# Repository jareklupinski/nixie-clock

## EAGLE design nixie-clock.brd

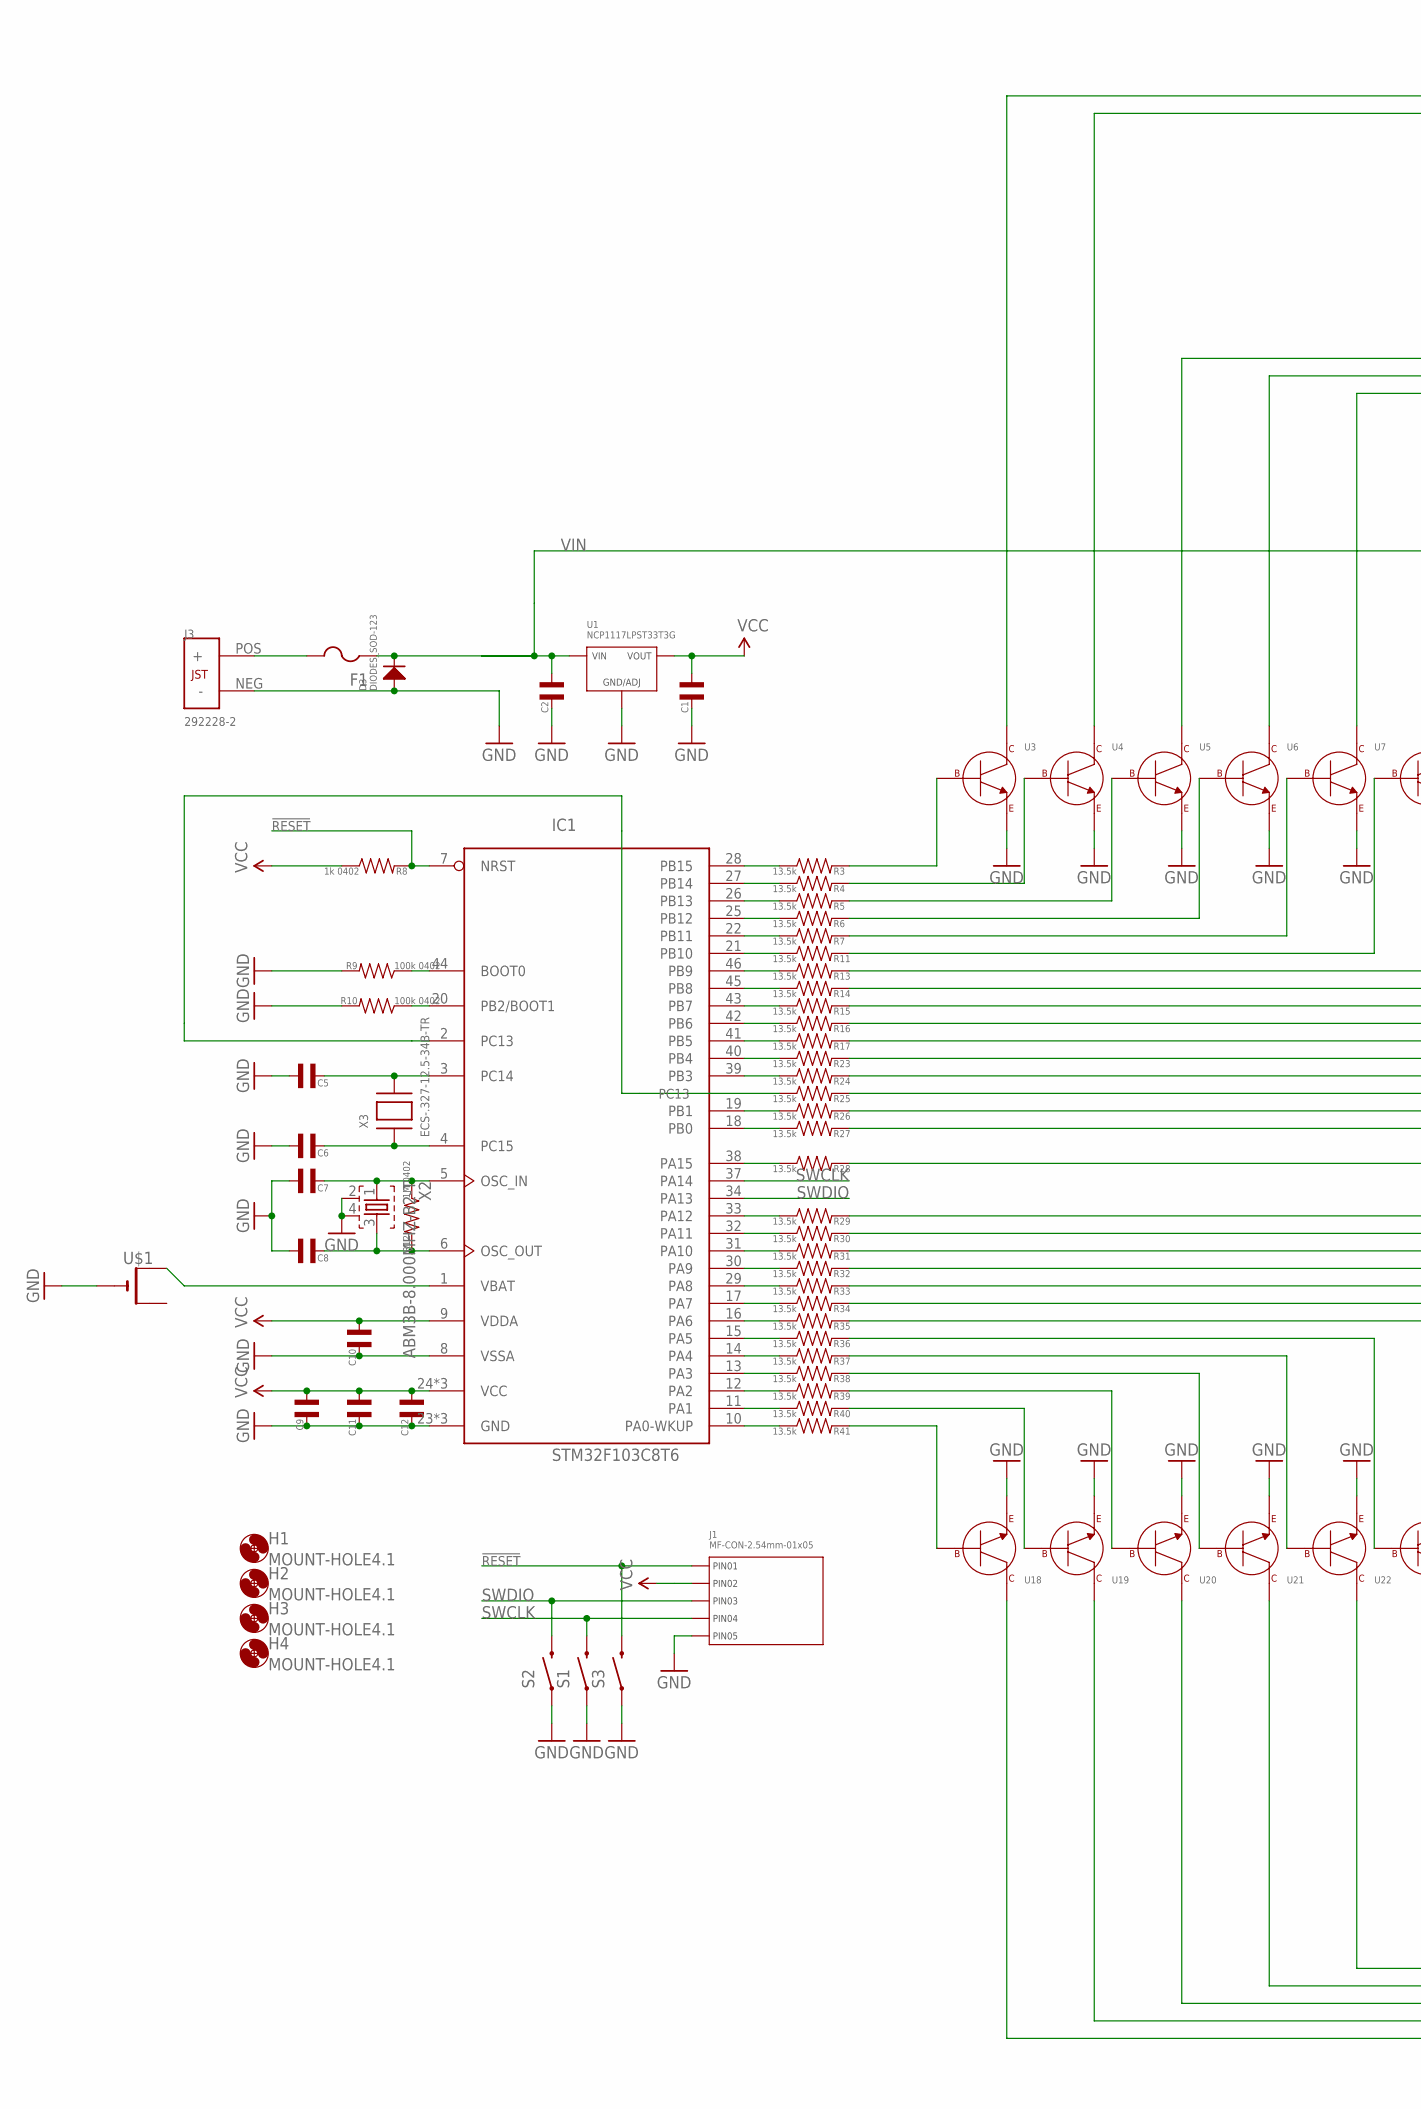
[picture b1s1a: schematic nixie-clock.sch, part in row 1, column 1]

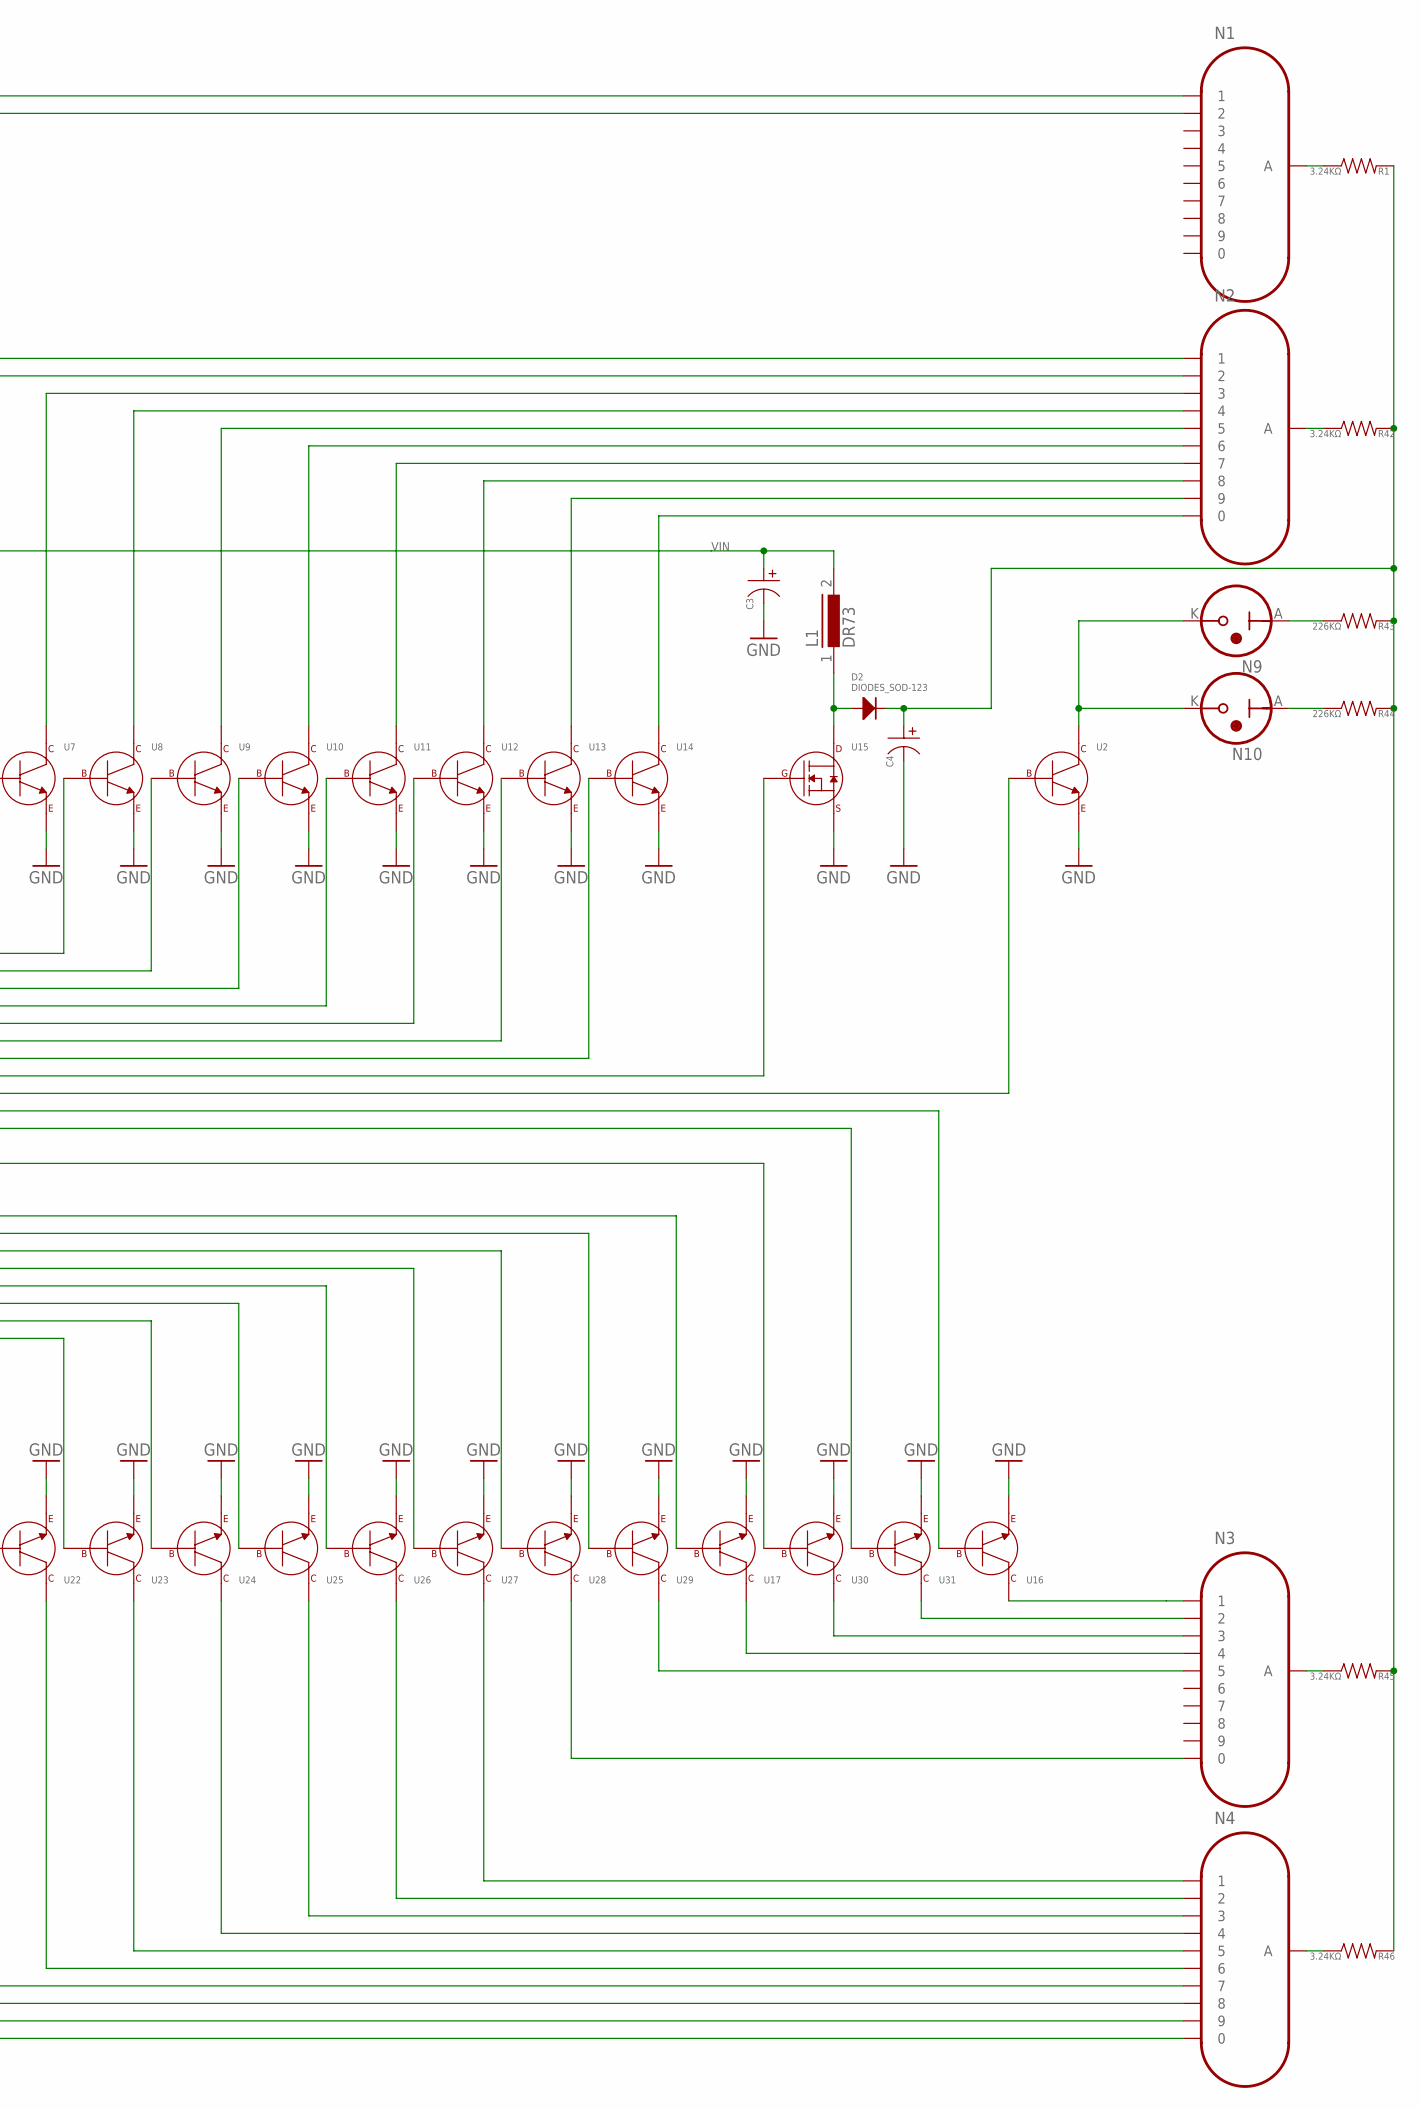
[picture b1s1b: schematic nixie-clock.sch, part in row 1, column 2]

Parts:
C1, C2: CAPACITOR_NP_1206; C1206
C3, C4: CAPACITOR_P_6.3MM; CP6.3MM
C5, C6, C7, C8, C9, C10, C11, C12: CAPACITOR_NP_0402; C0402
D2, D3: DIODES_SOD-123; SOD-123
F1: PTCFUSE-1812; 1812
H1, H2, H3, H4: MOUNT-HOLE4.1; 4,1
IC1: STM32F103C8T6; LQFP48
J1: MF-CON-2.54mm-01x05; PTH_2.54MM_01X05
J3: 292228-2
L1: DR73
N1: Hour1; IN-4
N2: Hour2; IN-4
N3: Minutes1; IN-4
N4: Minutes2; IN-4
N9: RainyBulb; INS-1
N10: SnowyBulb; INS-1
R1, R42, R45, R46: 3.24KΩ; R0402
R3, R4, R5, R6, R7, R11, R13, R14, R15, R16, R17, R23, R24, R25, R26, R27, R28, R29, R30, R31, R32, R33, R34, R35, R36, R37, R38, R39, R40, R41: 13.5k; R0402
R8: 1k 0402; R0402
R9, R10: 100k 0402; R0402
R12: 1M 0402; R0402
R43, R44: 226KΩ; R0402
S1, S2, S3: SWITCH-MOMENTARY-2TACTILE-SWITCH-SMD-RIGHT-ANGLE; TACTILE_SWITCH-SMD-RIGHT-ANGLE
U1: NCP1117LPST33T3G; SOT-223-3
U2, U3, U4, U5, U6, U7, U8, U9, U10, U11, U12, U13, U14, U16, U17, U18, U19, U20, U21, U22, U23, U24, U25, U26, U27, U28, U29, U30, U31: NPN_BJT_SOT-23-3; SOT-23-3
U15: N-CHANNEL_FET_TO-252-3; TO-252-3
U$1: CR1220SMT; CR1220-SMD
X2: ABM3B-8.000MHZ-B2-T; 5.2X3.4-4-PAD
X3: ECS-.327-12.5-34B-TR; XTAL3215

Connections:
!RESET: IC1.7 (NRST), J1.P$1 (PIN1), R8.P$2, S3.2
GND: C1.P$2, C2.P$2, C3.P$2, C4.P$2, C5.P$1, C6.P$1, C7.P$1, C8.P$1, C9.P$2, C10.P$2, C11.P$2, C12.P$2, D3.ANODE, IC1.8 (VSSA), IC1.23 (GND), IC1.35 (GND), IC1.47 (GND), J1.P$5 (PIN5), J3.NEG (-), R9.P$2, R10.P$2, S1.1, S2.1, S3.1, U1.P$2 (GND/ADJ), U2.P$2 (EMITTER), U3.P$2 (EMITTER), U4.P$2 (EMITTER), U5.P$2 (EMITTER), U6.P$2 (EMITTER), U7.P$2 (EMITTER), U8.P$2 (EMITTER), U9.P$2 (EMITTER), U10.P$2 (EMITTER), U11.P$2 (EMITTER), U12.P$2 (EMITTER), U13.P$2 (EMITTER), U14.P$2 (EMITTER), U15.2 (SOURCE), U16.P$2 (EMITTER), U17.P$2 (EMITTER), U18.P$2 (EMITTER), U19.P$2 (EMITTER), U20.P$2 (EMITTER), U21.P$2 (EMITTER), U22.P$2 (EMITTER), U23.P$2 (EMITTER), U24.P$2 (EMITTER), U25.P$2 (EMITTER), U26.P$2 (EMITTER), U27.P$2 (EMITTER), U28.P$2 (EMITTER), U29.P$2 (EMITTER), U30.P$2 (EMITTER), U31.P$2 (EMITTER), U$1.-, X2.2, X2.4
HV: C4.P$1, D2.CATHODE, R1.P$2, R42.P$2, R43.P$2, R44.P$2, R45.P$2, R46.P$2
HV1: N1.4 (A), R1.P$1
HV2: N2.4 (A), R42.P$1
HV3: N3.4 (A), R45.P$1
HV4: N4.4 (A), R46.P$1
unnamed: IC1.28 (PB15), R3.P$1
unnamed: IC1.27 (PB14), R4.P$1
unnamed: IC1.26 (PB13), R5.P$1
unnamed: IC1.25 (PB12), R6.P$1
unnamed: IC1.22 (PB11), R7.P$1
unnamed: IC1.21 (PB10), R11.P$1
unnamed: IC1.46 (PB9), R13.P$1
unnamed: IC1.45 (PB8), R14.P$1
unnamed: IC1.43 (PB7), R15.P$1
unnamed: IC1.42 (PB6), R16.P$1
unnamed: IC1.41 (PB5), R17.P$1
unnamed: IC1.40 (PB4), R23.P$1
unnamed: IC1.39 (PB3), R24.P$1
unnamed: IC1.19 (PB1), R26.P$1
unnamed: IC1.18 (PB0), R27.P$1
unnamed: IC1.38 (PA15), R28.P$1
unnamed: IC1.33 (PA12), R29.P$1
unnamed: IC1.32 (PA11), R30.P$1
unnamed: IC1.31 (PA10), R31.P$1
unnamed: IC1.30 (PA9), R32.P$1
unnamed: IC1.29 (PA8), R33.P$1
unnamed: IC1.17 (PA7), R34.P$1
unnamed: IC1.16 (PA6), R35.P$1
unnamed: IC1.15 (PA5), R36.P$1
unnamed: IC1.14 (PA4), R37.P$1
unnamed: IC1.13 (PA3), R38.P$1
unnamed: IC1.12 (PA2), R39.P$1
unnamed: IC1.11 (PA1), R40.P$1
unnamed: IC1.10 (PA0-WKUP), R41.P$1
unnamed: R3.P$2, U3.P$1 (BASE)
unnamed: IC1.20 (PB2/BOOT1), R10.P$1
unnamed: IC1.44 (BOOT0), R9.P$1
unnamed: D2.ANODE, L1.1, U15.PAD (DRAIN)
unnamed: N9.A, R43.P$1
unnamed: N10.A, R44.P$1
unnamed: C5.P$2, IC1.3 (PC14), X3.P$2
unnamed: C6.P$2, IC1.4 (PC15), X3.P$1
unnamed: C7.P$2, IC1.5 (OSC_IN), R12.P$1, X2.1
unnamed: C8.P$2, IC1.6 (OSC_OUT), R12.P$2, X2.3
unnamed: R4.P$2, U4.P$1 (BASE)
unnamed: IC1.1 (VBAT), U$1.+$1 (+)
unnamed: R5.P$2, U5.P$1 (BASE)
unnamed: R6.P$2, U6.P$1 (BASE)
unnamed: R7.P$2, U7.P$1 (BASE)
unnamed: R11.P$2, U8.P$1 (BASE)
unnamed: N1.14 (1), U3.P$3 (COLLECTOR)
unnamed: N1.9 (2), U4.P$3 (COLLECTOR)
unnamed: N2.14 (1), U5.P$3 (COLLECTOR)
unnamed: N2.9 (2), U6.P$3 (COLLECTOR)
unnamed: N2.11 (3), U7.P$3 (COLLECTOR)
unnamed: N2.1 (4), U8.P$3 (COLLECTOR)
unnamed: N2.12 (5), U9.P$3 (COLLECTOR)
unnamed: N2.2 (6), U10.P$3 (COLLECTOR)
unnamed: N2.6 (7), U11.P$3 (COLLECTOR)
unnamed: R13.P$2, U9.P$1 (BASE)
unnamed: R14.P$2, U10.P$1 (BASE)
unnamed: R15.P$2, U11.P$1 (BASE)
unnamed: N2.3 (8), U12.P$3 (COLLECTOR)
unnamed: N2.5 (9), U13.P$3 (COLLECTOR)
unnamed: N2.8 (0), U14.P$3 (COLLECTOR)
unnamed: R16.P$2, U12.P$1 (BASE)
unnamed: R17.P$2, U13.P$1 (BASE)
unnamed: R23.P$2, U14.P$1 (BASE)
unnamed: R24.P$2, U15.1 (GATE)
unnamed: R25.P$2, U2.P$1 (BASE)
unnamed: R26.P$2, U16.P$1 (BASE)
unnamed: F1.2, J3.POS (+)
unnamed: N9.K, N10.K, U2.P$3 (COLLECTOR)
unnamed: N3.14 (1), U16.P$3 (COLLECTOR)
unnamed: R41.P$2, U18.P$1 (BASE)
unnamed: R40.P$2, U19.P$1 (BASE)
unnamed: R39.P$2, U20.P$1 (BASE)
unnamed: R38.P$2, U21.P$1 (BASE)
unnamed: R37.P$2, U22.P$1 (BASE)
unnamed: R36.P$2, U23.P$1 (BASE)
unnamed: R35.P$2, U24.P$1 (BASE)
unnamed: R34.P$2, U25.P$1 (BASE)
unnamed: R33.P$2, U26.P$1 (BASE)
unnamed: R32.P$2, U27.P$1 (BASE)
unnamed: R31.P$2, U28.P$1 (BASE)
unnamed: R30.P$2, U29.P$1 (BASE)
unnamed: R29.P$2, U17.P$1 (BASE)
unnamed: R28.P$2, U30.P$1 (BASE)
unnamed: R27.P$2, U31.P$1 (BASE)
unnamed: N3.9 (2), U31.P$3 (COLLECTOR)
unnamed: N3.11 (3), U30.P$3 (COLLECTOR)
unnamed: N3.1 (4), U17.P$3 (COLLECTOR)
unnamed: N3.12 (5), U29.P$3 (COLLECTOR)
unnamed: N3.8 (0), U28.P$3 (COLLECTOR)
unnamed: N4.14 (1), U27.P$3 (COLLECTOR)
unnamed: N4.9 (2), U26.P$3 (COLLECTOR)
unnamed: N4.11 (3), U25.P$3 (COLLECTOR)
unnamed: N4.1 (4), U24.P$3 (COLLECTOR)
unnamed: N4.12 (5), U23.P$3 (COLLECTOR)
unnamed: N4.2 (6), U22.P$3 (COLLECTOR)
unnamed: N4.6 (7), U21.P$3 (COLLECTOR)
unnamed: N4.3 (8), U20.P$3 (COLLECTOR)
unnamed: N4.5 (9), U19.P$3 (COLLECTOR)
unnamed: N4.8 (0), U18.P$3 (COLLECTOR)
PC13: IC1.2 (PC13), R25.P$1
SWCLK: IC1.37 (PA14), J1.P$4 (PIN4), S1.2
SWDIO: IC1.34 (PA13), J1.P$3 (PIN3), S2.2
VCC: C1.P$1, C9.P$1, C10.P$1, C11.P$1, C12.P$1, IC1.9 (VDDA), IC1.24 (VCC), IC1.36 (VCC), IC1.48 (VCC), J1.P$2 (PIN2), R8.P$1, U1.P$1 (VOUT), U1.P$3 (VOUT)
VIN: C2.P$1, C3.P$1, D3.CATHODE, F1.1, L1.2, U1.P$4 (VIN)

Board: 4 copper layers, 106 parts (0 on the bottom side), 111 nets, no tracks yet.

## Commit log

2018-07-24 design in testing

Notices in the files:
parts and their libraries:
SparkFun-Aesthetics: Licensing: CC v3.0 Share-Alike You are welcome to use this library for commercial purposes.
